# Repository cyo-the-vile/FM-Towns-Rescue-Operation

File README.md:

# FM-Towns-Rescue-Operation
Study and Analysis of the Proprietary FM Towns Desktop CD-ROM drives.

This repository is a running analysis of the proprietary CD-ROM drive in Fujitsu's legendary computer the FM Towns. The intent is to study the embedded protocols in the CD-ROM drive with the long term intent to make an optical drive emulator. Over 97% of the software for the FM Towns computer is based on CD-ROM and with no new lasers around or with lasers being embedded in very expensive and old Technics CD-ROM players it isn't sustainable to cannibalize the laser from a player.

# Disc drive types

Thank you to Sampson for taking the time to photograph his three different drives.

There are three primary CD-ROM drives in the FM Towns desktop computer.

***********************************

The EA Desktop uses the two speed drive.

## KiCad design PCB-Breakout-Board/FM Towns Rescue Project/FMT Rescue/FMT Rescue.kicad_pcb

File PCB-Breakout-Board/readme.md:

# Breakout Board

The intention of the breakout board is to study and analyze the CD-ROM drive communication protocols used between CD-ROM drive and FMT computer. Kicad files for editing are also in the repository.

Most Desktop drives used a 64 Pin ASIC or custom microcontroller. This in all essence is a black box with no real pinout easily identifiable.

It is expected there should be i2s pins for CDDA, pins for subchannel data from the CD-ROM and then pins for data transfer likely a form of SPI.

# If you are interested grab the gerber files and send to the factory.  There is already a zipped copy ready to use for a factory.

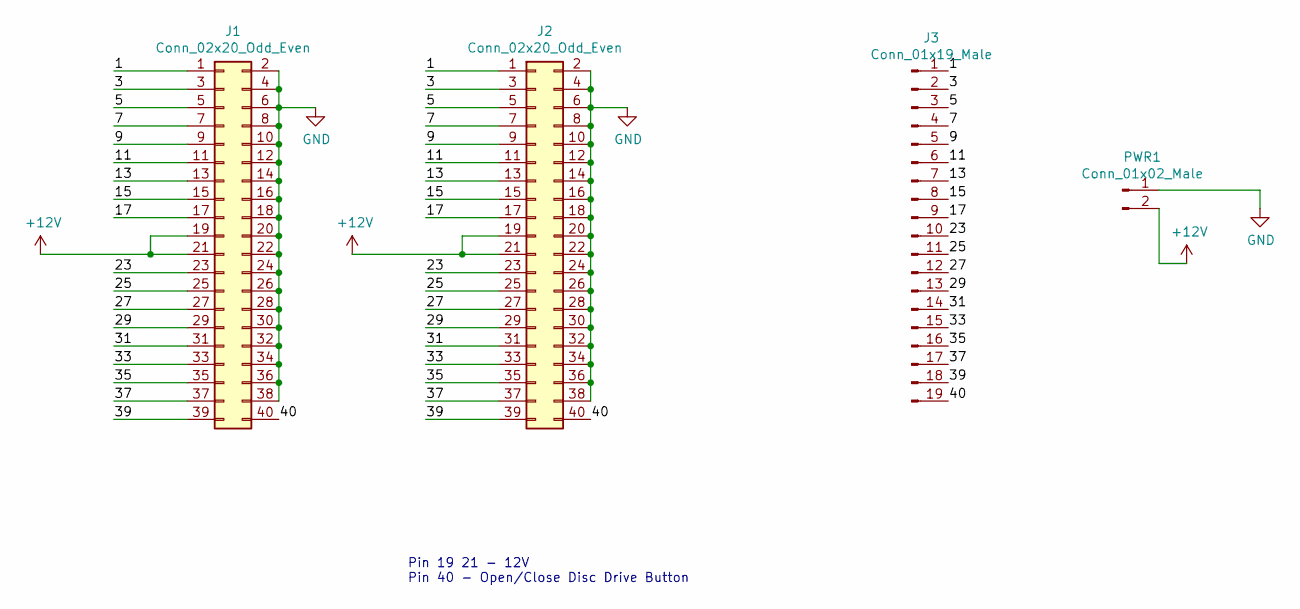
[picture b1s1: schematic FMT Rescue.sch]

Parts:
J1, J2: Conn_02x20_Odd_Even; PinHeader_2x20_P2.54mm_Vertical
J3: Conn_01x19_Male; PinSocket_1x19_P2.54mm_Vertical
PWR1: Conn_01x02_Male; PinHeader_1x02_P2.54mm_Vertical

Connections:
+12V: J1.19, J1.21, J2.19, J2.21, PWR1.2
/1: J1.1, J2.1, J3.1
/3: J1.3, J2.3, J3.2
/5: J1.5, J2.5, J3.3
/7: J1.7, J2.7, J3.4
/9: J1.9, J2.9, J3.5
/11: J1.11, J2.11, J3.6
/13: J1.13, J2.13, J3.7
/15: J1.15, J2.15, J3.8
/17: J1.17, J2.17, J3.9
/23: J1.23, J2.23, J3.10
/25: J1.25, J2.25, J3.11
/27: J1.27, J2.27, J3.12
/29: J1.29, J2.29, J3.13
/31: J1.31, J2.31, J3.14
/33: J1.33, J2.33, J3.15
/35: J1.35, J2.35, J3.16
/37: J1.37, J2.37, J3.17
/39: J1.39, J2.39, J3.18
/40: J1.40, J2.40, J3.19
GND: J1.2, J1.4, J1.6, J1.8, J1.10, J1.12, J1.14, J1.16, J1.18, J1.20, J1.22, J1.24, J1.26, J1.28, J1.30, J1.32, J1.34, J1.36, J1.38, J2.2, J2.4, J2.6, J2.8, J2.10, J2.12, J2.14, J2.16, J2.18, J2.20, J2.22, J2.24, J2.26, J2.28, J2.30, J2.32, J2.34, J2.36, J2.38, PWR1.1

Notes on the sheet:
Pin 19 21 - 12V Pin 40 - Open/Close Disc Drive Button

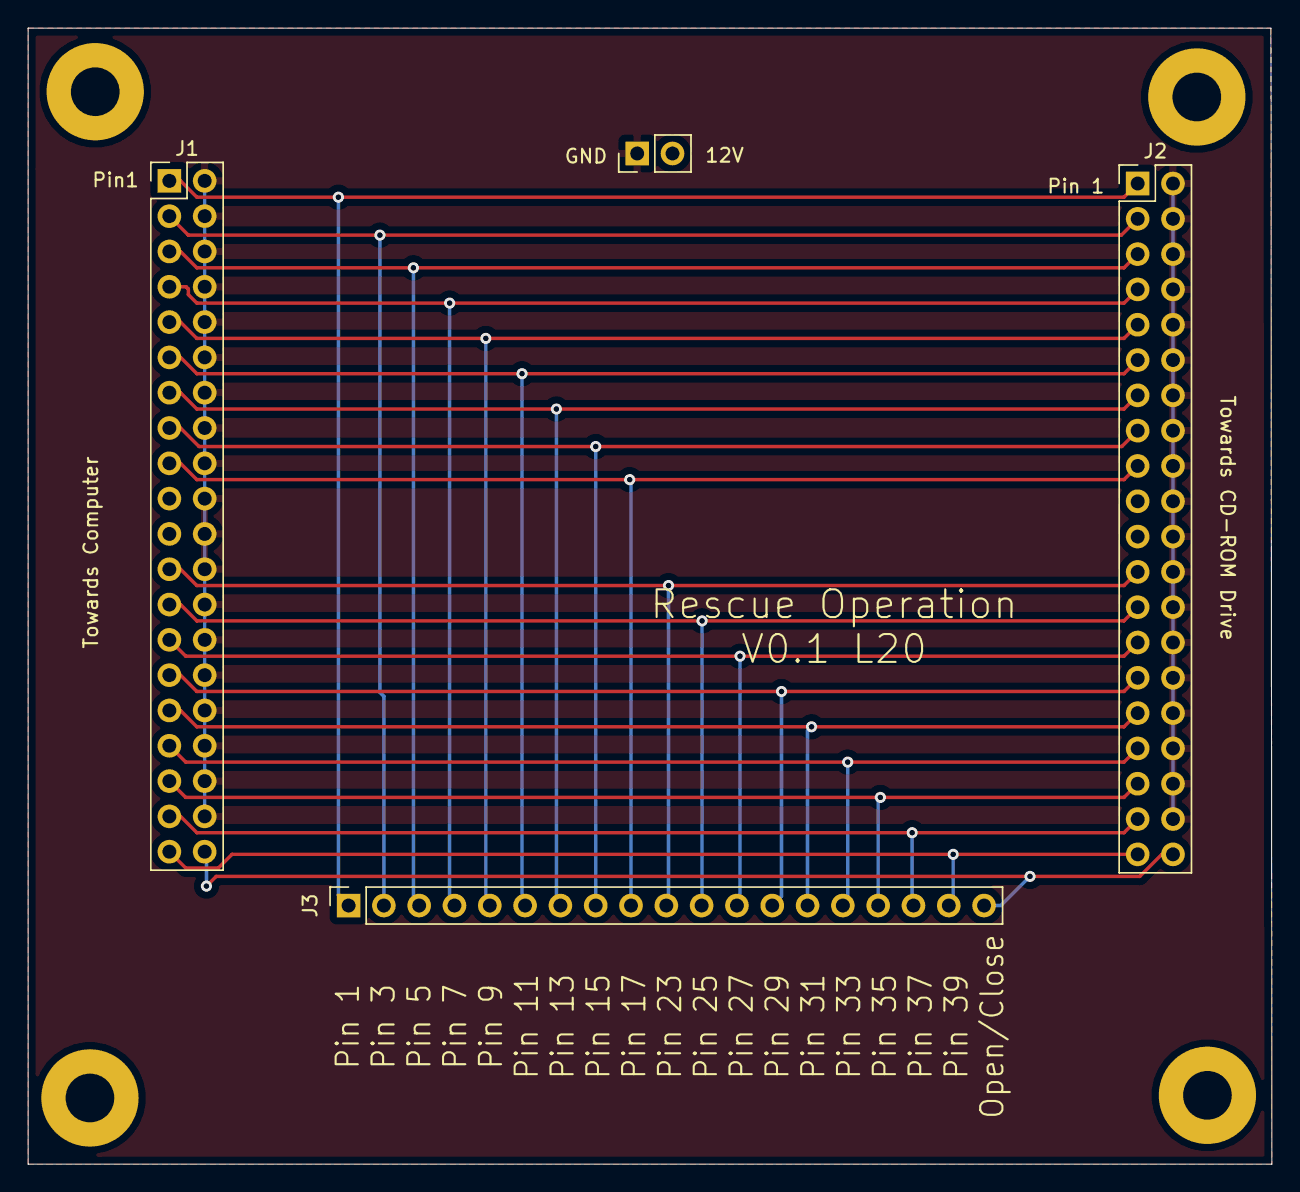
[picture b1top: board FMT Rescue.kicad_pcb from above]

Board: 2 copper layers, 89.5 x 81.7 mm, 4 parts (0 on the bottom side), 21 nets.

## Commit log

2022-03-29 Create photos
2022-03-29 Create Information
2022-03-30 Create PCB-Breakout-Board
